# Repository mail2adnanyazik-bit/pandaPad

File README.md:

This GitHub Repo contains the PCB, Schematics, 3D Models, Case, and etc. needed to build a "Pandapad",
a Macropad or Hackpad that is personalized to my (Im panda !) workflow, with 6 keys, an OLED, and a Rotary encoder
(in normie language thats a dial - the knob thing in old car radios)

To imitate this project you will need :

- my 3D printed case and plate
- A XIAO RP2040 Microcontroller, and a way to power it (usb-c cable)
- 6 switches (hopefully also keycaps lol), a rotary encoder and a 0.91" OLED (the schematics, pcb and 3d models for all of these are in the repo !)
- my PCB (again, this is in the repo !)
- a soldering iron

This project was done using the Hackpad tutorial and resources for the Hack Club event Stardance

I will be using the 6 Keys for :

- My mac hyperkey (Capslock becomes Cmd + Shift + Ctrl + Alt/Options) as an extra key
- Full screenshot
- Section Screenshot
- Copy
- Paste
- Undo

Rotary encoder for volume up/down and press for mute

For now the OLED will show only static text as i dont have a good idea what to display yet.

# CAD model :

Everything fits together with M3x16mm Screws

It has 2 seperate 3D printed pieces : The Top plate, and the case body in which the components sit

Made with OnShape

# PCB

This is my PCB :

My schematic :

Both were designed in KiCad

# Firmware :

## Rotary encoder :

Volume up/down, mute

## Keys 1 - 6 (in order) :

- 1 : Sends ⌃⌥⇧⌘ (Ctrl+Option+Shift+Cmd) – my Mac’s hyperkey
- 2 : Sends hyperkey + 2 → myShottr full screenshot keybind
- 3 : Sends hyperkey + 3 → Shottr region screenshot
- 4 : ⌘C (Copy)
- 5 : ⌘V (Paste)
- 6 : ⌘Z (Undo)

# BOM :

Here should be everything you need to make this macropad :

- 6 x Cherry MX Switches
- 6 x DSA Keycaps
- 1 x 0.91" 128x32 OLED Display
- 1 x EC11 Rotary Encoder
- 1 x XIAO RP2040 Microcontroller
- 1 x Case (2 3D printed parts)

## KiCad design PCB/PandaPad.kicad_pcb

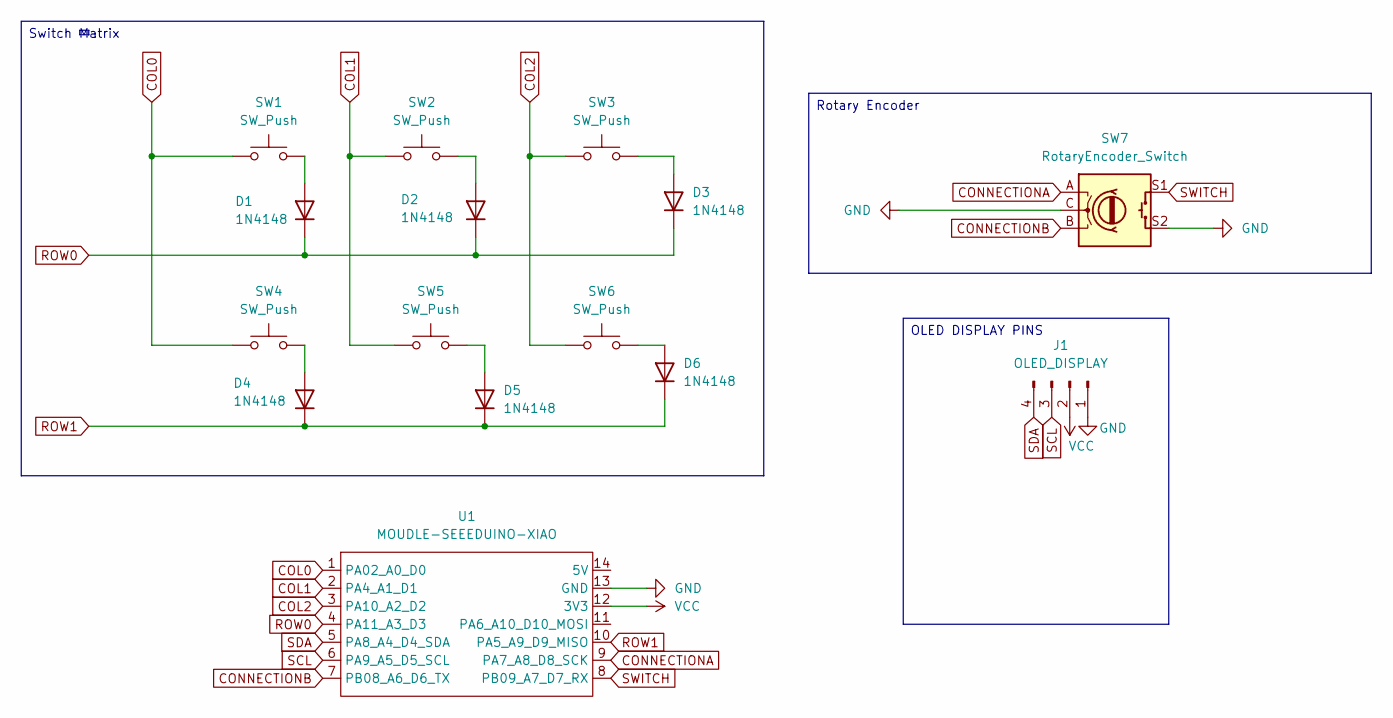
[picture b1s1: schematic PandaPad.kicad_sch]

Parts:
D1, D2, D3, D4, D5, D6: 1N4148; D_DO-35_SOD27_P7.62mm_Horizontal
J1: OLED_DISPLAY; SSD1306-0.91-OLED-4pin-128x32
SW1, SW2, SW3, SW4, SW5, SW6: SW_Push; SW_Cherry_MX_1.00u_PCB
SW7: RotaryEncoder_Switch; RotaryEncoder_Alps_EC11E-Switch_Vertical_H20mm
U1: MOUDLE-SEEEDUINO-XIAO; XIAO-Generic-Hybrid-14P-2.54-21X17.8MM

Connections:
COL0: SW1.1, SW4.1, U1.1 (PA02_A0_D0)
COL1: SW2.1, SW5.1, U1.2 (PA4_A1_D1)
COL2: SW3.1, SW6.1, U1.3 (PA10_A2_D2)
CONNECTIONA: SW7.A, U1.9 (PA7_A8_D8_SCK)
CONNECTIONB: SW7.B, U1.7 (PB08_A6_D6_TX)
GND: J1.1, SW7.C, SW7.S2, U1.13 (GND)
unnamed: D1.2 (A), SW1.2
unnamed: D2.2 (A), SW2.2
unnamed: D3.2 (A), SW3.2
unnamed: D4.2 (A), SW4.2
unnamed: D5.2 (A), SW5.2
unnamed: D6.2 (A), SW6.2
ROW0: D1.1 (K), D2.1 (K), D3.1 (K), U1.4 (PA11_A3_D3)
ROW1: D4.1 (K), D5.1 (K), D6.1 (K), U1.10 (PA5_A9_D9_MISO)
SCL: J1.3, U1.6 (PA9_A5_D5_SCL)
SDA: J1.4, U1.5 (PA8_A4_D4_SDA)
SWITCH: SW7.S1, U1.8 (PB09_A7_D7_RX)
VCC: J1.2, U1.12 (3V3)

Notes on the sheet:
OLED DISPLAY PINS
Switch Matrix
Rotary Encoder

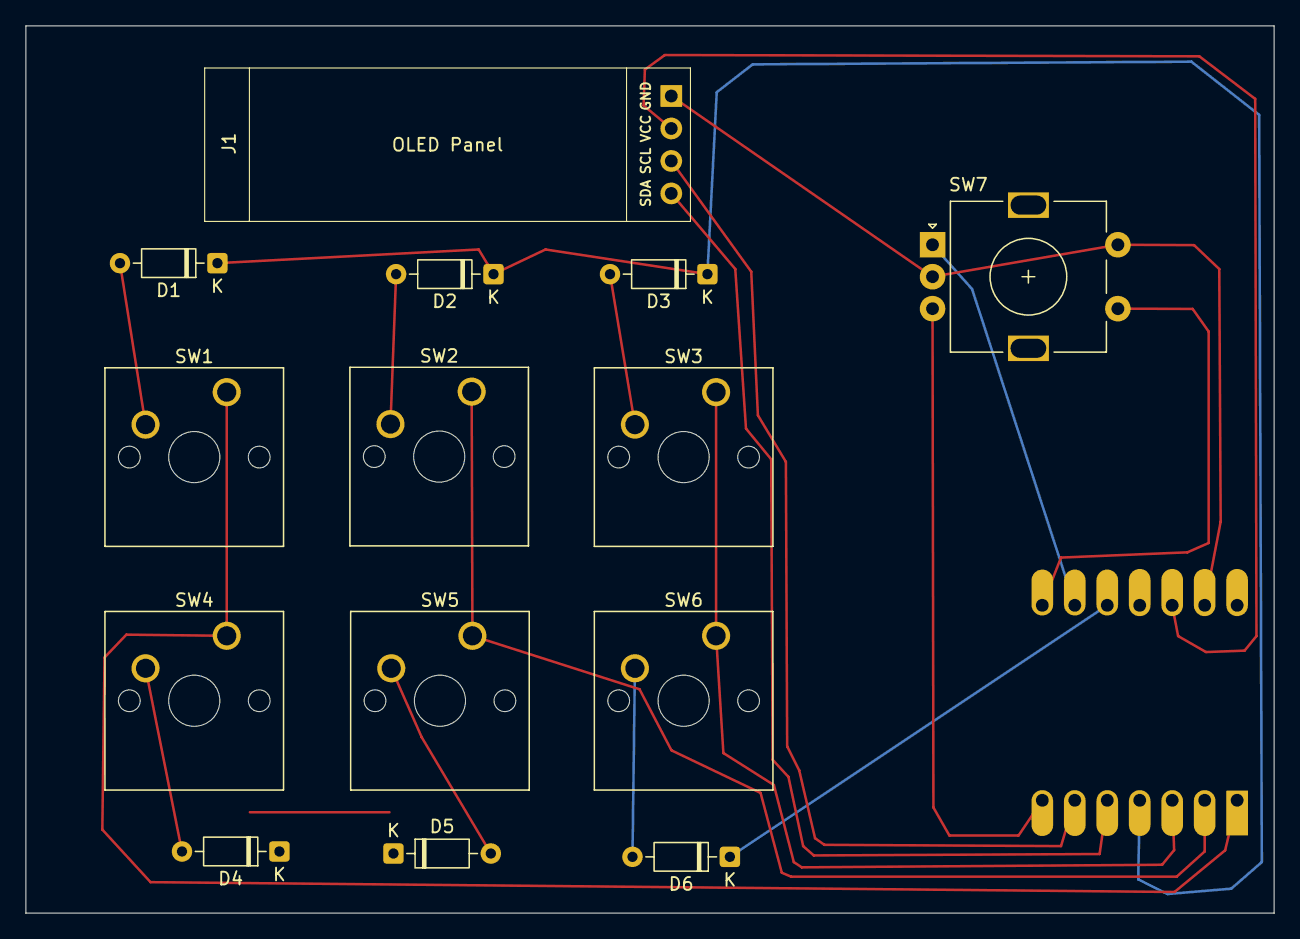
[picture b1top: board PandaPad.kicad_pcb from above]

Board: 2 copper layers, 97.6 x 69.4 mm, 15 parts (1 on the bottom side), 18 nets.

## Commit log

2026-06-15 reworked file structure
2026-06-15 Update README with CAD, PCB, firmware, and BOM details
    Added CAD model, PCB details, firmware functions, and BOM for the macropad.
2026-06-16 added .uf2 file for production
2026-06-16 changed production files to fit the criteria
2026-06-16 fixed small error in the final assembly, and deleted unnecessary file from production folder
2026-06-16 fixed README formatting mistake
